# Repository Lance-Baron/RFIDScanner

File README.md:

Here is a project, where we try to make a RFID Scanner, where we make a custome PCB, Antenna, and write all the code. The Code folder contains all of the files needed to program the microcontrollers, and the ECAD folder contains all of the KiCad Files in for the project.

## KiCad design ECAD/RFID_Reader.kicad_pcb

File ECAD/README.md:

These are the KiCad Files that Lance Baron has been working on locally.

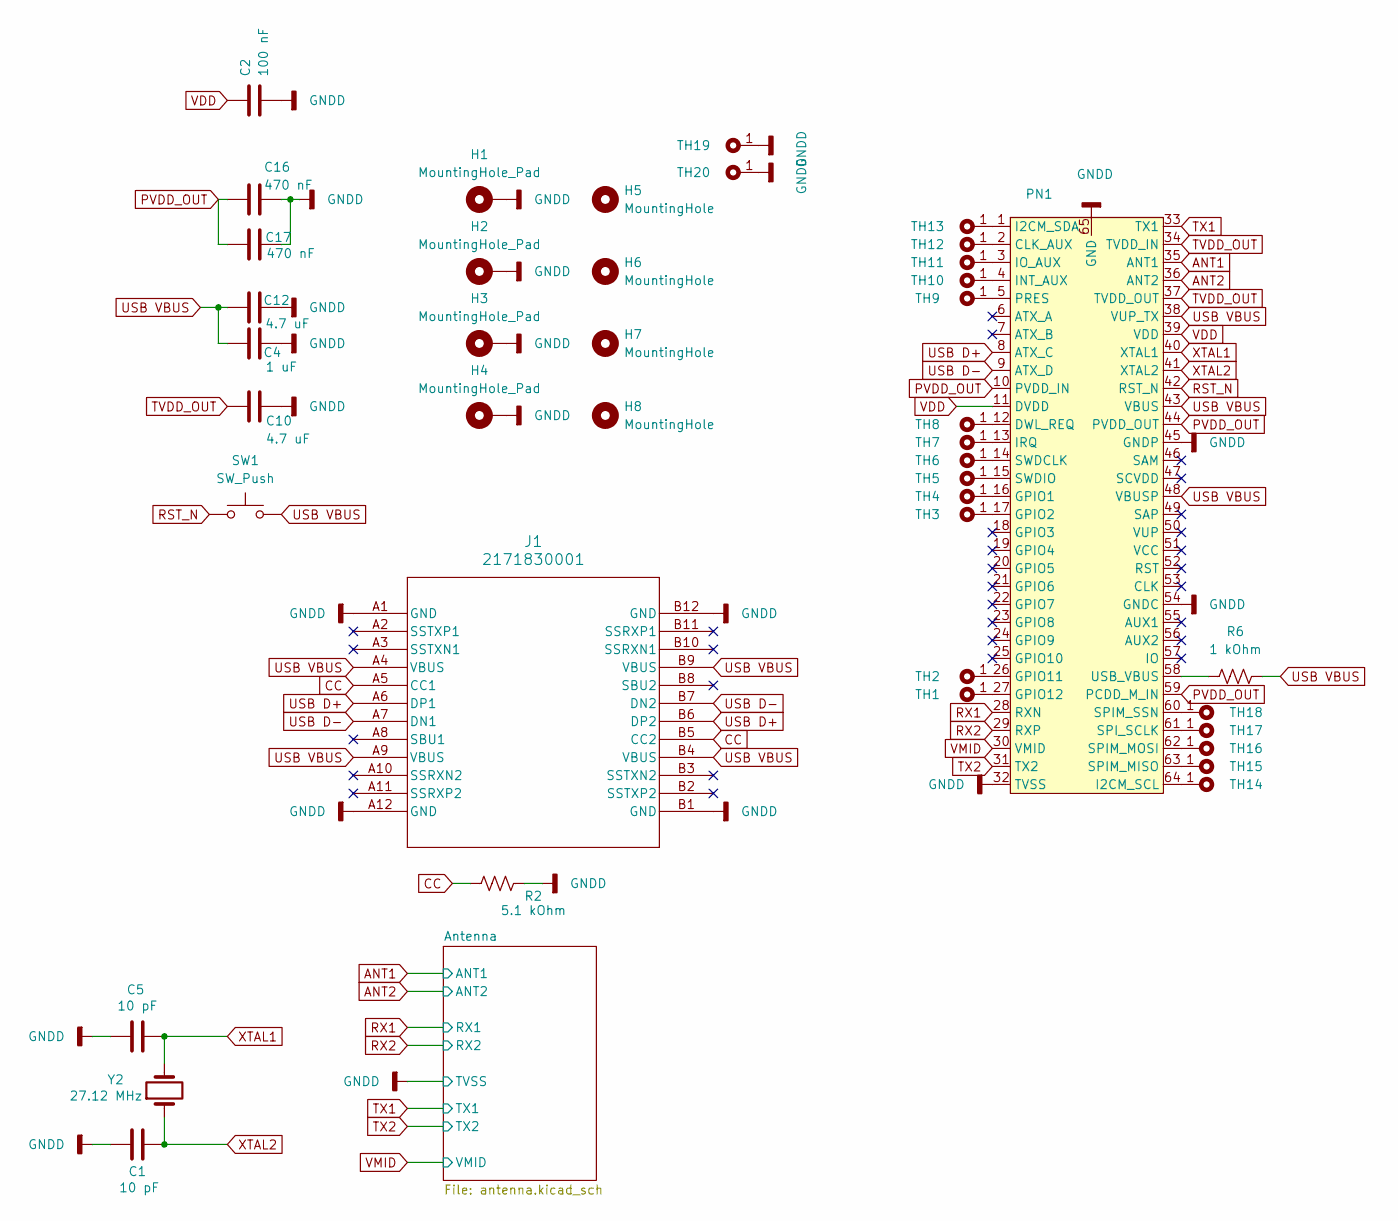
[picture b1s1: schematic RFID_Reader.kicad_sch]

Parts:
C1, C5: 10 pF; C_0805_2012Metric
C2: 100 nF; C_0805_2012Metric
C4: 1 uF; C_0805_2012Metric
C10, C12: 4.7 uF; C_0805_2012Metric
C16, C17: 470 nF; C_0805_2012Metric
H1, H2, H3, H4: MountingHole_Pad; MountingHole_3.5mm_Pad
H5, H6, H7, H8: MountingHole; MountingHole_60mil
J1: 2171830001; CONN_2171830001_MOL
PN1: QFN50P900X900X100-65N-D
R2: 5.1 kOhm; R_0805_2012Metric
R6: 1 kOhm; R_0805_2012Metric
SW1: SW_Push; SW_PUSH_6mm
TH1, TH2, TH3, TH4, TH5, TH6, TH7, TH8, TH9, TH10, TH11, TH12, TH13, TH14, TH15, TH16, TH17, TH18, TH19, TH20: TH22
Y2: 27.12 MHz; Crystal_SMD_0603-2Pin_6.0x3.5mm_HandSoldering

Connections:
ANT1: PN1.35 (ANT1); also elsewhere on the board
ANT2: PN1.36 (ANT2); also elsewhere on the board
CC: J1.A5 (CC1), J1.B5 (CC2), R2.1
GNDD: C1.2, C2.2, C4.1, C5.2, C10.2, C12.2, C16.2, C17.2, H1.1, H2.1, H3.1, H4.1, J1.A1 (GND), J1.A12 (GND), J1.B1 (GND), J1.B12 (GND), PN1.32 (TVSS), PN1.45 (GNDP), PN1.54 (GNDC), PN1.65 (GND), R2.2, TH19.1, TH20.1; also elsewhere on the board
unnamed: PN1.2 (CLK_AUX), TH12.1
unnamed: PN1.12 (DWL_REQ), TH8.1
unnamed: PN1.16 (GPIO1), TH4.1
unnamed: PN1.17 (GPIO2), TH3.1
unnamed: PN1.26 (GPIO11), TH2.1
unnamed: PN1.27 (GPIO12), TH1.1
unnamed: PN1.64 (I2CM_SCL), TH14.1
unnamed: PN1.1 (I2CM_SDA), TH13.1
unnamed: PN1.4 (INT_AUX), TH10.1
unnamed: PN1.3 (IO_AUX), TH11.1
unnamed: PN1.13 (IRQ), TH7.1
unnamed: PN1.5 (PRES), TH9.1
unnamed: PN1.63 (SPIM_MISO), TH15.1
unnamed: PN1.62 (SPIM_MOSI), TH16.1
unnamed: PN1.60 (SPIM_SSN), TH18.1
unnamed: PN1.61 (SPI_SCLK), TH17.1
unnamed: PN1.14 (SWDCLK), TH6.1
unnamed: PN1.15 (SWDIO), TH5.1
unnamed: PN1.58 (USB_VBUS), R6.1
PVDD_OUT: C16.1, C17.1, PN1.10 (PVDD_IN), PN1.44 (PVDD_OUT), PN1.59 (PCDD_M_IN)
RST_N: PN1.42 (RST_N), SW1.1
RX1: PN1.28 (RXN); also elsewhere on the board
RX2: PN1.29 (RXP); also elsewhere on the board
TVDD_OUT: C10.1, PN1.34 (TVDD_IN), PN1.37 (TVDD_OUT)
TX1: PN1.33 (TX1); also elsewhere on the board
TX2: PN1.31 (TX2); also elsewhere on the board
USB D+: J1.A6 (DP1), J1.B6 (DP2), PN1.8 (ATX_C)
USB D-: J1.A7 (DN1), J1.B7 (DN2), PN1.9 (ATX_D)
USB VBUS: C4.2, C12.1, J1.A4 (VBUS), J1.A9 (VBUS), J1.B4 (VBUS), J1.B9 (VBUS), PN1.38 (VUP_TX), PN1.43 (VBUS), PN1.48 (VBUSP), R6.2, SW1.2
VDD: C2.1, PN1.11 (DVDD), PN1.39 (VDD)
VMID: PN1.30 (VMID); also elsewhere on the board
XTAL1: C5.1, PN1.40 (XTAL1), Y2.2
XTAL2: C1.1, PN1.41 (XTAL2), Y2.1

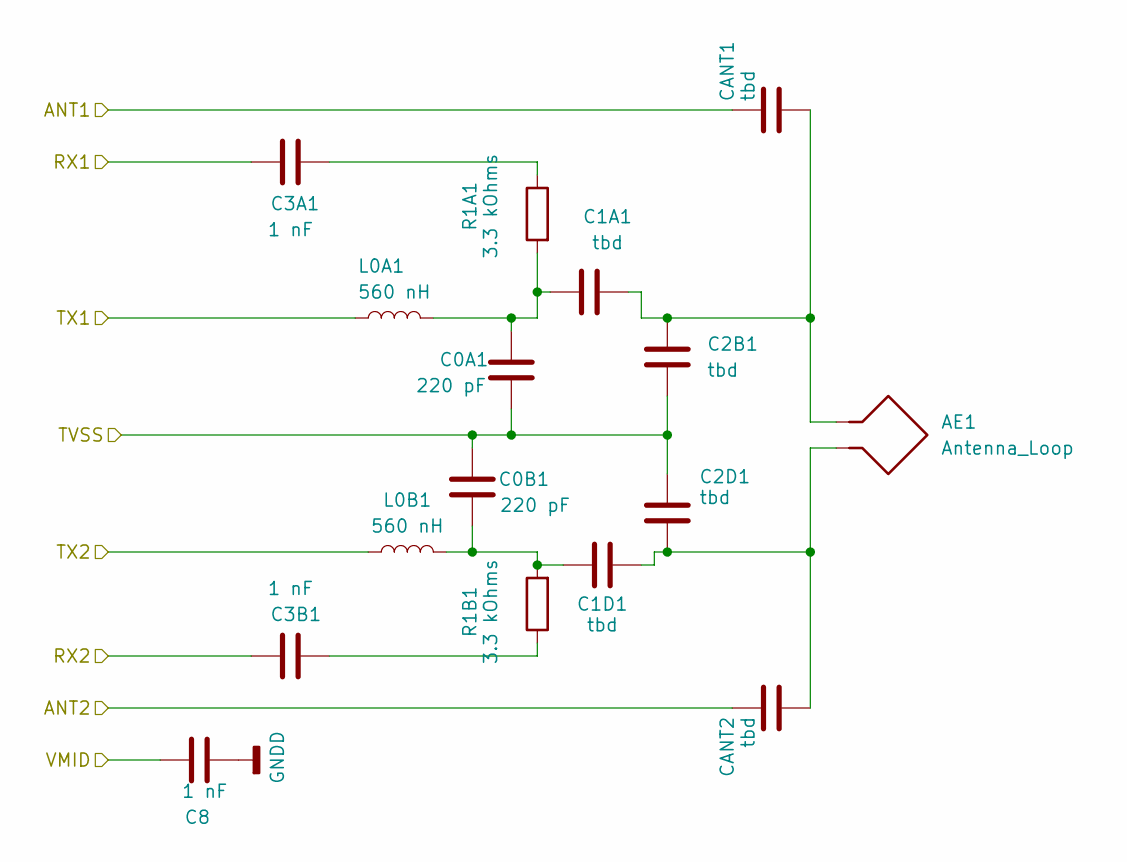
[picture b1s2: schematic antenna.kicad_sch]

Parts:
AE1: Antenna_Loop; JST_PH_B2B-PH-K_1x02_P2.00mm_Vertical
C0A1, C0B1: 220 pF; C_0805_2012Metric
C1A1, C1D1, C2B1, C2D1: tbd; C_0805_2012Metric
C3A1, C3B1, C8: 1 nF; C_0805_2012Metric
CANT1, CANT2: tbd; C_0805_2012Metric
L0A1, L0B1: 560 nH; L_0805_2012Metric
R1A1, R1B1: 3.3 kOhms; R_0805_2012Metric

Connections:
ANT1: CANT1.2; also elsewhere on the board
ANT2: CANT2.2; also elsewhere on the board
GNDD: C0A1.2, C0B1.2, C2B1.1, C2D1.2, C8.1; also elsewhere on the board
unnamed: AE1.1, C1A1.2, C2B1.2, CANT1.1
unnamed: AE1.2, C1D1.2, C2D1.1, CANT2.1
unnamed: C0A1.1, C1A1.1, L0A1.2, R1A1.2
unnamed: C0B1.1, C1D1.1, L0B1.2, R1B1.2
unnamed: C3A1.1, R1A1.1
unnamed: C3B1.1, R1B1.1
RX1: C3A1.2; also elsewhere on the board
RX2: C3B1.2; also elsewhere on the board
TX1: L0A1.1; also elsewhere on the board
TX2: L0B1.1; also elsewhere on the board
VMID: C8.2; also elsewhere on the board

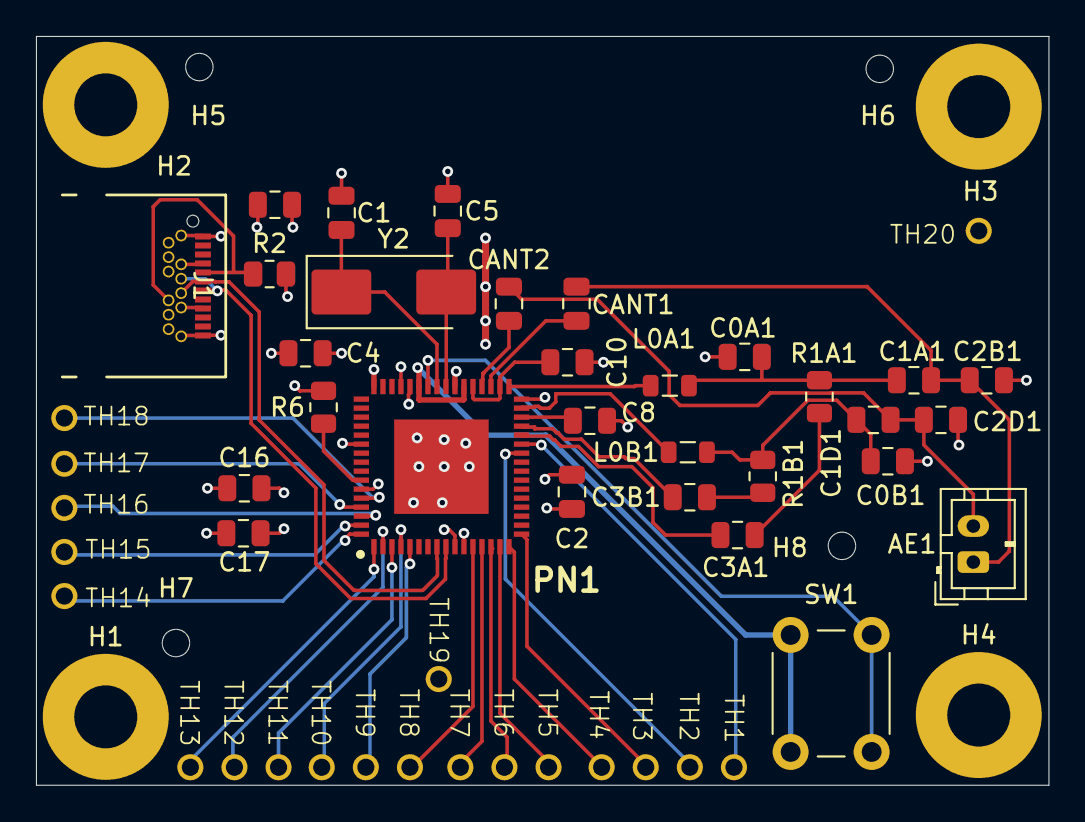
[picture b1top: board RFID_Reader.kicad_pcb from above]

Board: 4 copper layers, 56.2 x 41.6 mm, 58 parts (0 on the bottom side), 43 nets.

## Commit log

2026-02-20 Initial Commit for Project Formation
2026-02-20 Add project description for RFID Scanner
2026-02-20 Added to the README File
2026-02-20 Fixed Capitilization Error
2026-02-20 Moved original code into Code Folder
2026-02-20 Added KiCAD caches to gitignore
2026-02-20 Moved gitignore to main directory
2026-02-20 Added KiCadFiles
2026-02-20 Added README
2026-02-20 Moved, and updated the README
2026-03-09 Updated gitignore for ECAD files
2026-03-09 Added in Kicad Files
2026-03-09 Removed the Seperate Power Schematic
2026-03-27 Updated gitignore to ignore production files
2026-03-27 Updated schmatics
2026-04-17 Changed Schematic
2026-04-17 Added Example Code from leaked github repo
